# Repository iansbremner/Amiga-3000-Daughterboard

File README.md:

# Amiga-3000-Daughterboard
This is a recreation of the Rev 9 Daughterboard for the Amiga 3000
This is a 4 Layer board with signal on the upper and lower layers and a Power and Ground Plane.

When fabbing the board you will probably be asked if you want to remove the solder mask on the area for the Edge Connectors. It is fine to say Yes to this.

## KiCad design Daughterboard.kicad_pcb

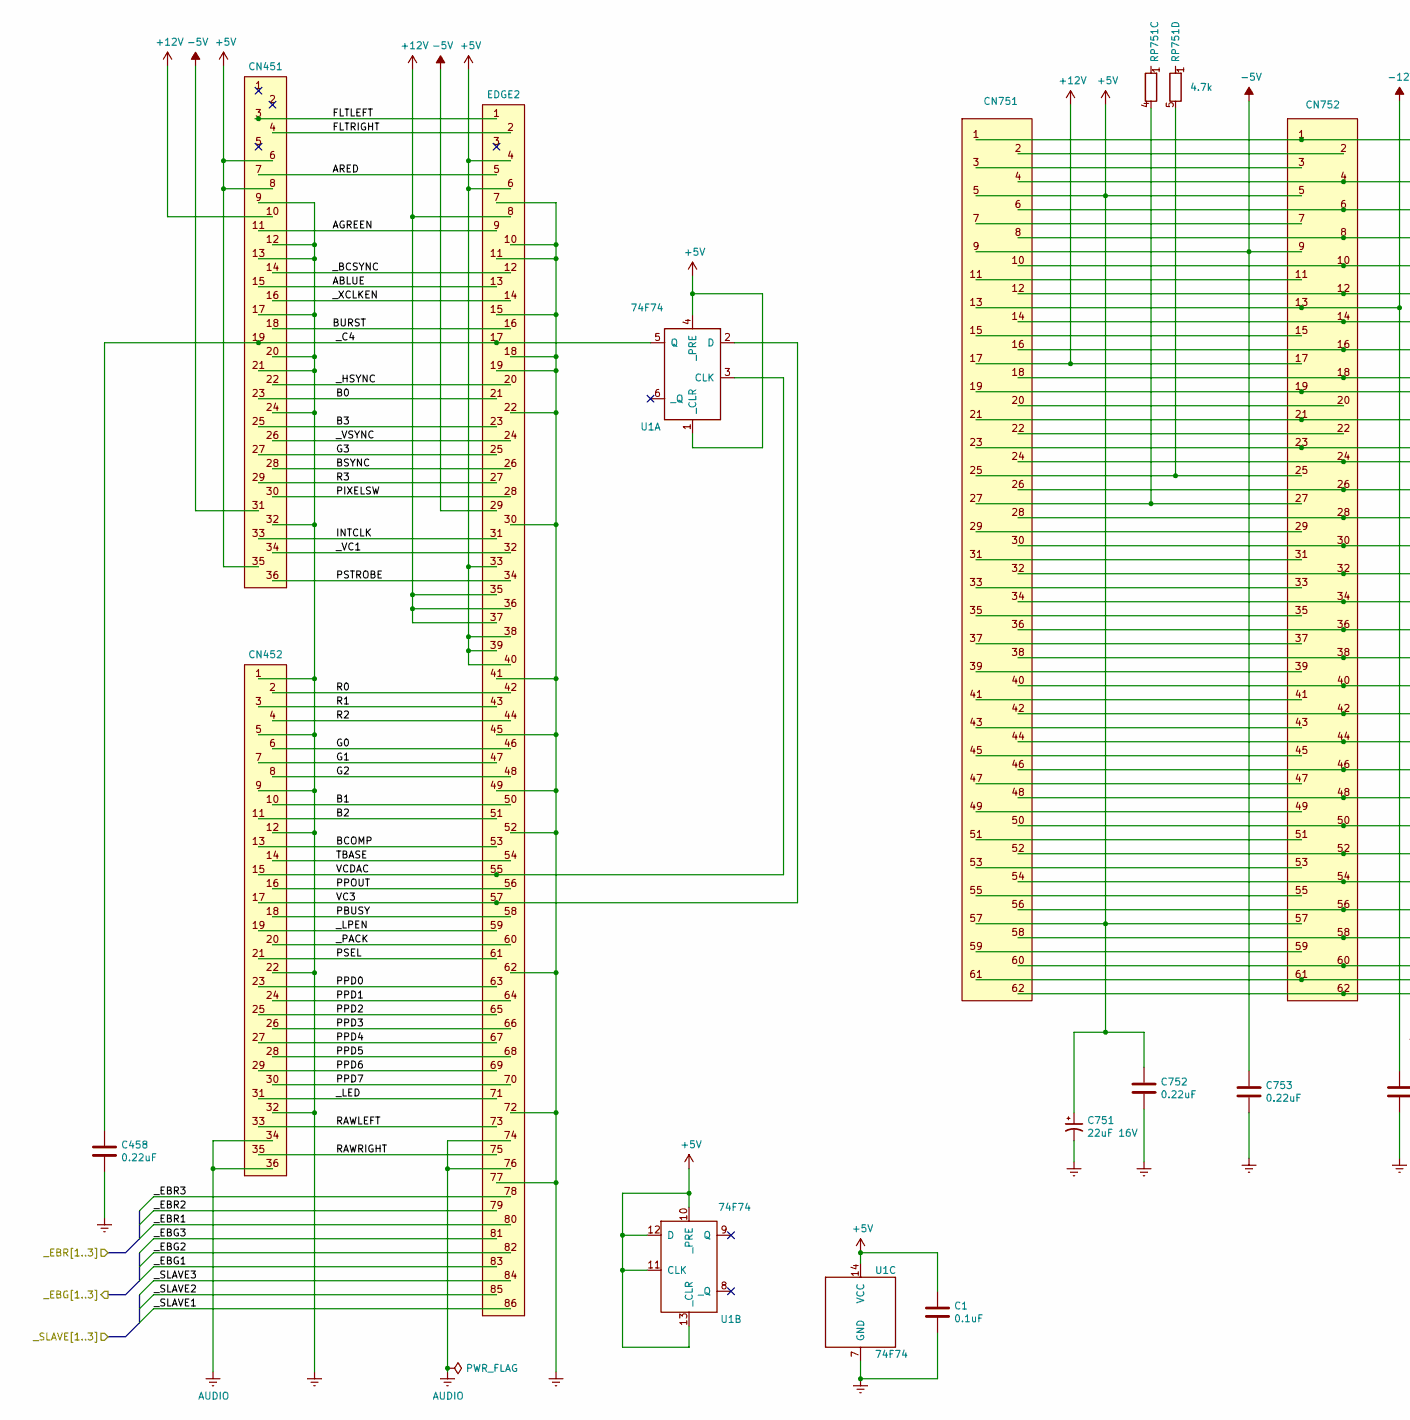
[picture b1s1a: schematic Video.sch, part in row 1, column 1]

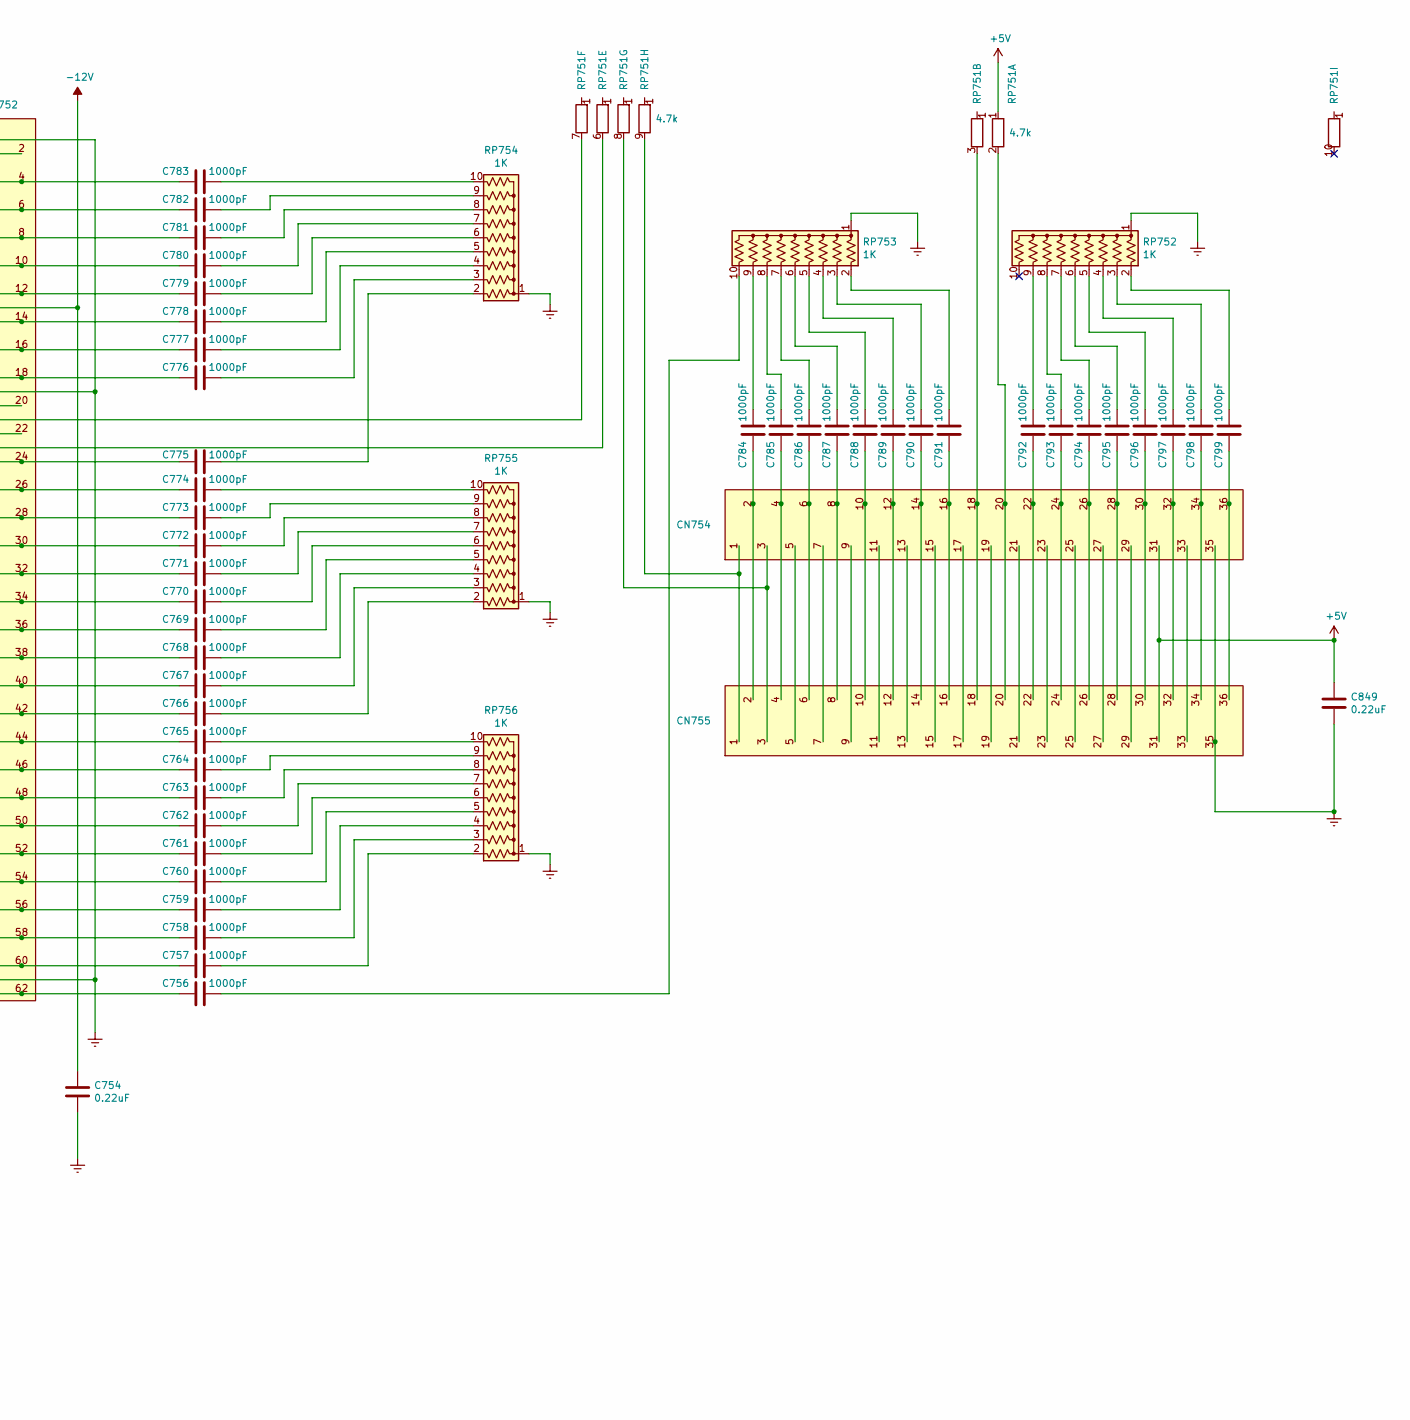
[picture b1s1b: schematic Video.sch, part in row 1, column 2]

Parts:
C1: 0.1uF; C_Axial_L5.1mm_D3.1mm_P7.50mm_Horizontal
C458, C752, C753, C754, C849: 0.22uF; C_Disc_D7.0mm_W2.5mm_P5.00mm
C751: 22uF 16V; CP_Radial_D8.0mm_P5.00mm
C756, C757, C758, C759, C760, C761, C762, C763, C764, C765, C766, C767, C768, C769, C770, C771, C772, C773, C774, C775, C776, C777, C778, C779, C780, C781, C782, C783, C784, C785, C786, C787, C788, C789, C790, C791, C792, C793, C794, C795, C796, C797, C798, C799: 1000pF; C_Rect_L4.6mm_W2.0mm_P2.50mm_MKS02_FKP02
CN451, CN452: Video_Slot; Video Slot
CN751, CN752: ISA_8_Bit; ISA 8 Bit
CN754, CN755: ISA_16_Bit_Extended; ISA 16 Bit
EDGE2: Edge2; Edge1
RP751: 4.7k; R_Array_SIP10
RP752, RP753, RP754, RP755, RP756: 1K; R_Array_SIP10
U1: 74F74; DIP-14_W7.62mm

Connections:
+5V: C1.1, C751.1, C752.1, C849.1, CN451.6, CN451.8, CN451.35, CN751.5, CN751.57, CN752.5, CN752.57, CN754.31, CN755.31, EDGE2.4, EDGE2.6, EDGE2.33, EDGE2.38, EDGE2.39, EDGE2.40, RP751.1 (R1.1), U1.1 (_CLR), U1.4 (_PRE), U1.10 (_PRE), U1.11 (CLK), U1.12 (D), U1.13 (_CLR), U1.14 (VCC); also elsewhere on the board
+12V: CN451.10, CN751.17, CN752.17, EDGE2.8, EDGE2.35, EDGE2.36, EDGE2.37; also elsewhere on the board
-5V: C753.1, CN451.31, CN751.9, CN752.9, EDGE2.29; also elsewhere on the board
-12V: C754.1, CN751.13, CN752.13; also elsewhere on the board
/Video & ISA/ABLUE: CN451.15, EDGE2.13
/Video & ISA/AGREEN: CN451.11, EDGE2.9
/Video & ISA/ARED: CN451.7, EDGE2.5
/Video & ISA/B0: CN451.23, EDGE2.21
/Video & ISA/B1: CN452.10, EDGE2.50
/Video & ISA/B2: CN452.11, EDGE2.51
/Video & ISA/B3: CN451.25, EDGE2.23
/Video & ISA/BCOMP: CN452.13, EDGE2.53
/Video & ISA/BSYNC: CN451.28, EDGE2.26
/Video & ISA/BURST: CN451.18, EDGE2.16
/Video & ISA/FLTLEFT: CN451.3, EDGE2.1
/Video & ISA/FLTRIGHT: CN451.4, EDGE2.2
/Video & ISA/G0: CN452.6, EDGE2.46
/Video & ISA/G1: CN452.7, EDGE2.47
/Video & ISA/G2: CN452.8, EDGE2.48
/Video & ISA/G3: CN451.27, EDGE2.25
/Video & ISA/INTCLK: CN451.33, EDGE2.31
/Video & ISA/PBUSY: CN452.18, EDGE2.58
/Video & ISA/PIXELSW: CN451.30, EDGE2.28
/Video & ISA/PPD0: CN452.23, EDGE2.63
/Video & ISA/PPD1: CN452.24, EDGE2.64
/Video & ISA/PPD2: CN452.25, EDGE2.65
/Video & ISA/PPD3: CN452.26, EDGE2.66
/Video & ISA/PPD4: CN452.27, EDGE2.67
/Video & ISA/PPD5: CN452.28, EDGE2.68
/Video & ISA/PPD6: CN452.29, EDGE2.69
/Video & ISA/PPD7: CN452.30, EDGE2.70
/Video & ISA/PPOUT: CN452.16, EDGE2.56
/Video & ISA/PSEL: CN452.21, EDGE2.61
/Video & ISA/PSTROBE: CN451.36, EDGE2.34
/Video & ISA/R0: CN452.2, EDGE2.42
/Video & ISA/R1: CN452.3, EDGE2.43
/Video & ISA/R2: CN452.4, EDGE2.44
/Video & ISA/R3: CN451.29, EDGE2.27
/Video & ISA/RAWLEFT: CN452.33, EDGE2.73
/Video & ISA/RAWRIGHT: CN452.35, EDGE2.75
/Video & ISA/TBASE: CN452.14, EDGE2.54
/Video & ISA/VC3: CN452.17, EDGE2.57, U1.2 (D)
/Video & ISA/VCDAC: CN452.15, EDGE2.55, U1.3 (CLK)
/Video & ISA/_BCSYNC: CN451.14, EDGE2.12
/Video & ISA/_C4: C458.1, CN451.19, EDGE2.17, U1.5 (Q)
/Video & ISA/_EBG1: EDGE2.83; also elsewhere on the board
/Video & ISA/_EBG2: EDGE2.82; also elsewhere on the board
/Video & ISA/_EBG3: EDGE2.81; also elsewhere on the board
/Video & ISA/_EBR1: EDGE2.80; also elsewhere on the board
/Video & ISA/_EBR2: EDGE2.79; also elsewhere on the board
/Video & ISA/_EBR3: EDGE2.78; also elsewhere on the board
/Video & ISA/_HSYNC: CN451.22, EDGE2.20
/Video & ISA/_LED: CN452.31, EDGE2.71
/Video & ISA/_LPEN: CN452.19, EDGE2.59
/Video & ISA/_PACK: CN452.20, EDGE2.60
/Video & ISA/_SLAVE1: EDGE2.86; also elsewhere on the board
/Video & ISA/_SLAVE2: EDGE2.85; also elsewhere on the board
/Video & ISA/_SLAVE3: EDGE2.84; also elsewhere on the board
/Video & ISA/_VC1: CN451.34, EDGE2.32
/Video & ISA/_VSYNC: CN451.26, EDGE2.24
/Video & ISA/_XCLKEN: CN451.16, EDGE2.14
AUDIO: CN452.34, CN452.36, EDGE2.74, EDGE2.76
Earth: C1.2, C458.2, C751.2, C752.2, C753.2, C754.2, C849.2, CN451.9, CN451.12, CN451.13, CN451.17, CN451.20, CN451.21, CN451.24, CN451.32, CN452.1, CN452.5, CN452.9, CN452.12, CN452.22, CN452.32, CN751.1, CN751.19, CN751.61, CN752.1, CN752.19, CN752.61, CN754.35, CN755.35, EDGE2.7, EDGE2.10, EDGE2.11, EDGE2.15, EDGE2.18, EDGE2.19, EDGE2.22, EDGE2.30, EDGE2.41, EDGE2.45, EDGE2.49, EDGE2.52, EDGE2.62, EDGE2.72, EDGE2.77, RP752.1 (common), RP753.1 (common), RP754.1 (common), RP755.1 (common), RP756.1 (common), U1.7 (GND); also elsewhere on the board
unnamed: C756.1, RP753.10 (R9)
unnamed: C756.2, CN751.62, CN752.62
unnamed: C757.1, RP756.2 (R1)
unnamed: C757.2, CN751.60, CN752.60
unnamed: C758.1, RP756.3 (R2)
unnamed: C758.2, CN751.58, CN752.58
unnamed: C759.1, RP756.4 (R3)
unnamed: C759.2, CN751.56, CN752.56
unnamed: C760.1, RP756.5 (R4)
unnamed: C760.2, CN751.54, CN752.54
unnamed: C761.1, RP756.6 (R5)
unnamed: C761.2, CN751.52, CN752.52
unnamed: C762.1, RP756.7 (R6)
unnamed: C762.2, CN751.50, CN752.50
unnamed: C763.1, RP756.8 (R7)
unnamed: C763.2, CN751.48, CN752.48
unnamed: C764.1, RP756.9 (R8)
unnamed: C764.2, CN751.46, CN752.46
unnamed: C765.1, RP756.10 (R9)
unnamed: C765.2, CN751.44, CN752.44
unnamed: C766.1, RP755.2 (R1)
unnamed: C766.2, CN751.42, CN752.42
unnamed: C767.1, RP755.3 (R2)
unnamed: C767.2, CN751.40, CN752.40
unnamed: C768.1, RP755.4 (R3)
unnamed: C768.2, CN751.38, CN752.38
unnamed: C769.1, RP755.5 (R4)
unnamed: C769.2, CN751.36, CN752.36
unnamed: C770.1, RP755.6 (R5)
unnamed: C770.2, CN751.34, CN752.34
unnamed: C771.1, RP755.7 (R6)
unnamed: C771.2, CN751.32, CN752.32
unnamed: C772.1, RP755.8 (R7)
unnamed: C772.2, CN751.30, CN752.30
unnamed: C773.1, RP755.9 (R8)
unnamed: C773.2, CN751.28, CN752.28
unnamed: C774.1, RP755.10 (R9)
unnamed: C774.2, CN751.26, CN752.26
unnamed: C775.1, RP754.2 (R1)
unnamed: C775.2, CN751.24, CN752.24
unnamed: C776.1, RP754.3 (R2)
unnamed: C776.2, CN751.18, CN752.18
unnamed: C777.1, RP754.4 (R3)
unnamed: C777.2, CN751.16, CN752.16
unnamed: C778.1, RP754.5 (R4)
unnamed: C778.2, CN751.14, CN752.14
unnamed: C779.1, RP754.6 (R5)
unnamed: C779.2, CN751.12, CN752.12
unnamed: C780.1, RP754.7 (R6)
unnamed: C780.2, CN751.10, CN752.10
unnamed: C781.1, RP754.8 (R7)
unnamed: C781.2, CN751.8, CN752.8
unnamed: C782.1, RP754.9 (R8)
unnamed: C782.2, CN751.6, CN752.6
unnamed: C783.1, RP754.10 (R9)
unnamed: C783.2, CN751.4, CN752.4
unnamed: C784.1, RP753.9 (R8)
unnamed: C784.2, CN754.2, CN755.2
unnamed: C785.1, RP753.8 (R7)
unnamed: C785.2, CN754.4, CN755.4
unnamed: C786.1, RP753.7 (R6)
unnamed: C786.2, CN754.6, CN755.6
unnamed: C787.1, RP753.6 (R5)
unnamed: C787.2, CN754.8, CN755.8
unnamed: C788.1, RP753.5 (R4)
unnamed: C788.2, CN754.10, CN755.10
unnamed: C789.1, RP753.4 (R3)
unnamed: C789.2, CN754.12, CN755.12
unnamed: C790.1, RP753.3 (R2)
unnamed: C790.2, CN754.14, CN755.14
unnamed: C791.1, RP753.2 (R1)
unnamed: C791.2, CN754.16, CN755.16
unnamed: C792.1, RP752.9 (R8)
unnamed: C792.2, CN754.22, CN755.22
unnamed: C793.1, RP752.8 (R7)
unnamed: C793.2, CN754.24, CN755.24
unnamed: C794.1, RP752.7 (R6)
unnamed: C794.2, CN754.26, CN755.26
unnamed: C795.1, RP752.6 (R5)
unnamed: C795.2, CN754.28, CN755.28
unnamed: C796.1, RP752.5 (R4)
unnamed: C796.2, CN754.30, CN755.30
unnamed: C797.1, RP752.4 (R3)
unnamed: C797.2, CN754.32, CN755.32
unnamed: C798.1, RP752.3 (R2)
unnamed: C798.2, CN754.34, CN755.34
unnamed: C799.1, RP752.2 (R1)
unnamed: C799.2, CN754.36, CN755.36
unnamed: CN751.2, CN752.2
unnamed: CN751.3, CN752.3
unnamed: CN751.7, CN752.7
unnamed: CN751.11, CN752.11
unnamed: CN751.15, CN752.15
unnamed: CN751.20, CN752.20
unnamed: CN751.21, CN752.21, RP751.7 (R6.2)
unnamed: CN751.22, CN752.22
unnamed: CN751.23, CN752.23, RP751.6 (R5.2)
unnamed: CN751.25, CN752.25, RP751.5 (R4.2)
unnamed: CN751.27, CN752.27, RP751.4 (R3.2)
unnamed: CN751.29, CN752.29
unnamed: CN751.31, CN752.31
unnamed: CN751.33, CN752.33
unnamed: CN751.35, CN752.35
unnamed: CN751.37, CN752.37
unnamed: CN751.39, CN752.39
unnamed: CN751.41, CN752.41
unnamed: CN751.43, CN752.43
unnamed: CN751.45, CN752.45
unnamed: CN751.47, CN752.47
unnamed: CN751.49, CN752.49
unnamed: CN751.51, CN752.51
unnamed: CN751.53, CN752.53
unnamed: CN751.55, CN752.55
unnamed: CN751.59, CN752.59
unnamed: CN754.1, CN755.1, RP751.9 (R8.2)
unnamed: CN754.3, CN755.3, RP751.8 (R7.2)
unnamed: CN754.5, CN755.5
unnamed: CN754.7, CN755.7
unnamed: CN754.9, CN755.9
unnamed: CN754.11, CN755.11
unnamed: CN754.13, CN755.13
unnamed: CN754.15, CN755.15
unnamed: CN754.17, CN755.17
unnamed: CN754.18, CN755.18, RP751.3 (R2.2)
unnamed: CN754.19, CN755.19
unnamed: CN754.20, CN755.20, RP751.2 (R1.2)
unnamed: CN754.21, CN755.21
unnamed: CN754.23, CN755.23
unnamed: CN754.25, CN755.25
unnamed: CN754.27, CN755.27
unnamed: CN754.29, CN755.29
unnamed: CN754.33, CN755.33

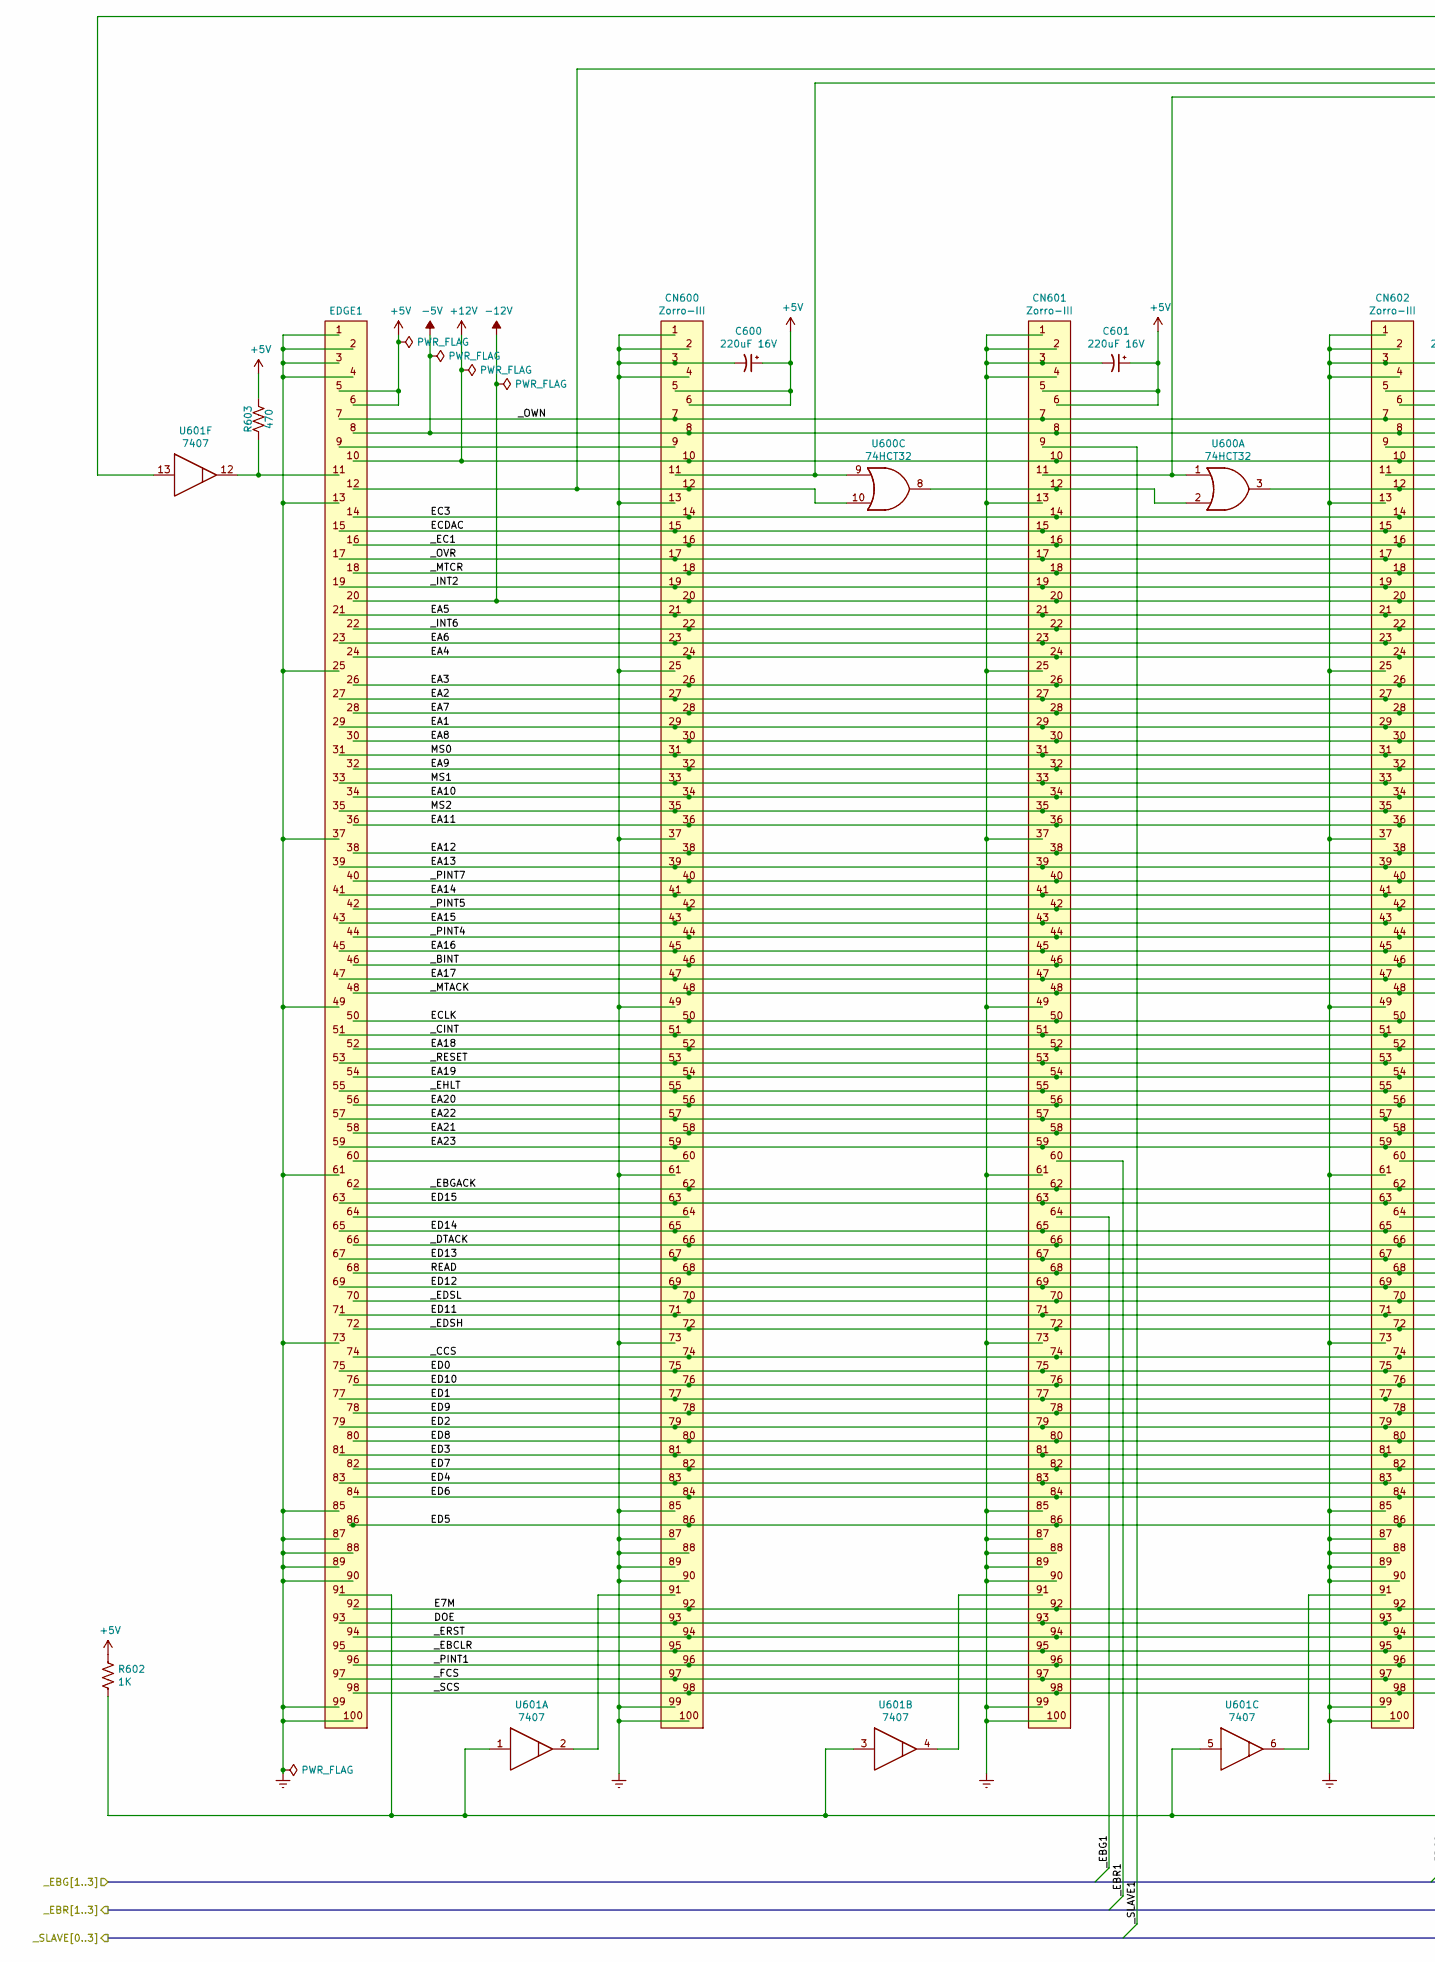
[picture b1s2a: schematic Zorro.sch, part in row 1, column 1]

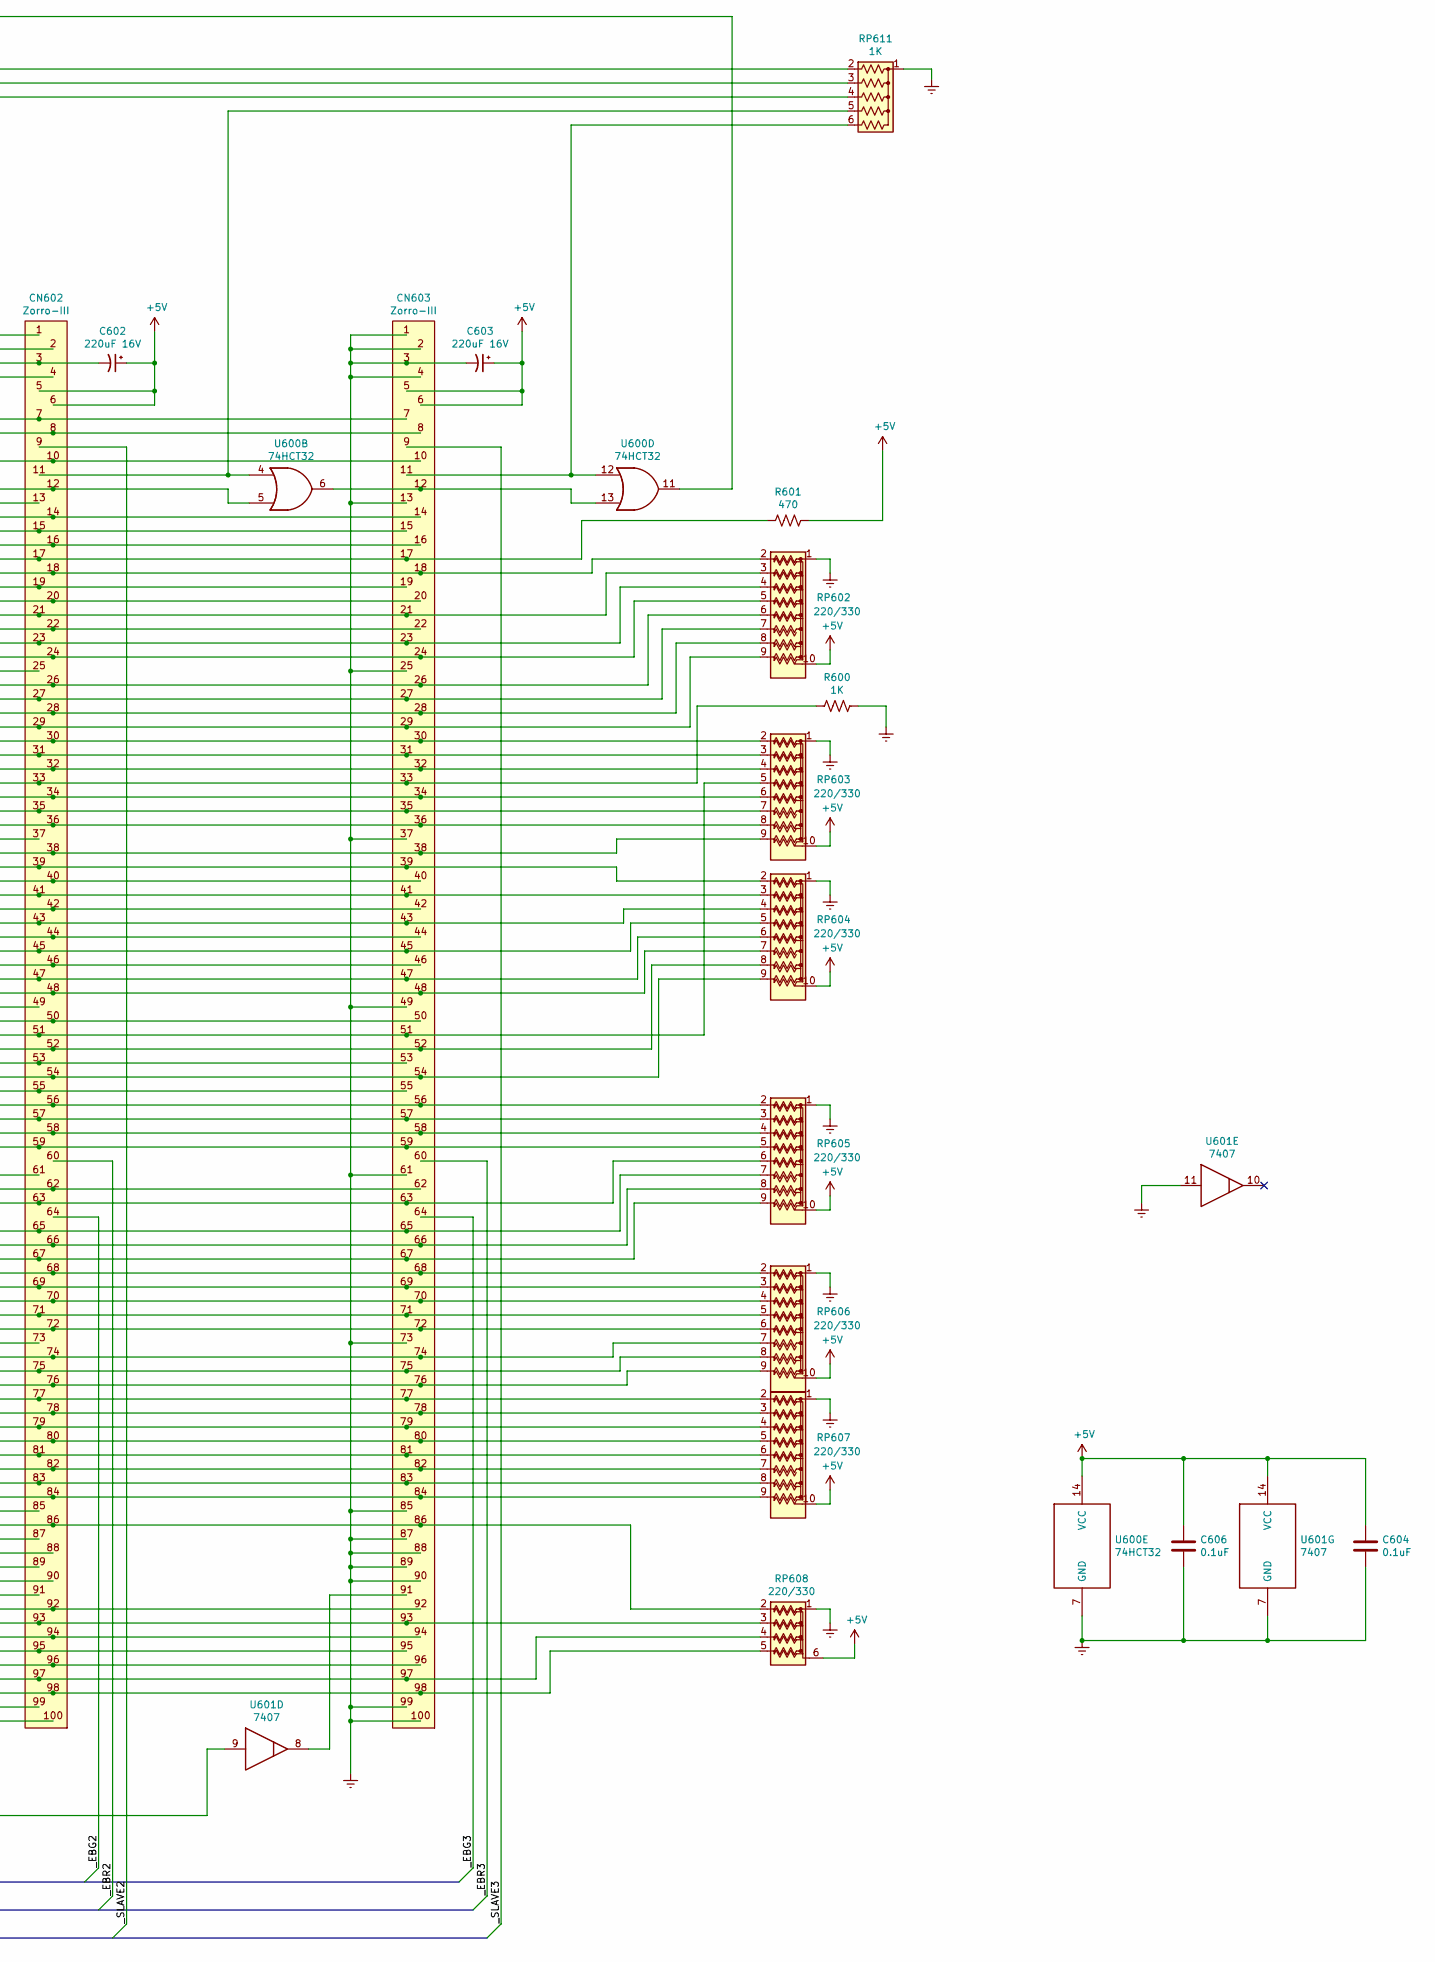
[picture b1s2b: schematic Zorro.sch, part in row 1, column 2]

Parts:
C600, C601, C602, C603: 220uF 16V; CP_Axial_L21.0mm_D8.0mm_P28.00mm_Horizontal
C604, C606: 0.1uF; C_Axial_L5.1mm_D3.1mm_P7.50mm_Horizontal
CN600, CN601, CN602, CN603: Zorro-III
EDGE1: Edge1; Edge2
R600, R602: 1K; Resistor
R601, R603: 470; Resistor
RP602, RP603, RP604, RP605, RP606, RP607: 220/330; R_Array_SIP10
RP608: 220/330; R_Array_SIP6
RP611: 1K; R_Array_SIP6
U600: 74HCT32; DIP-14_W7.62mm_Socket
U601: 7407; DIP-14_W7.62mm

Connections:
+5V: C600.1, C601.1, C602.1, C603.1, C604.1, C606.1, CN600.5, CN600.6, CN601.5, CN601.6, CN602.5, CN602.6, CN603.5, CN603.6, EDGE1.5, EDGE1.6, R601.1, R602.1, R603.1, RP602.10 (R7), RP603.10 (R7), RP604.10 (R7), RP605.10 (R7), RP606.10 (R7), RP607.10 (R7), RP608.6 (R7), U600.14 (VCC), U601.14 (VCC); also elsewhere on the board
+12V: CN600.10, CN601.10, CN602.10, CN603.10, EDGE1.10; also elsewhere on the board
-5V: CN600.8, CN601.8, CN602.8, CN603.8, EDGE1.8; also elsewhere on the board
-12V: CN600.20, CN601.20, CN602.20, CN603.20, EDGE1.20; also elsewhere on the board
/Video & ISA/_EBG1: CN601.64; also elsewhere on the board
/Video & ISA/_EBG2: CN602.64; also elsewhere on the board
/Video & ISA/_EBG3: CN603.64; also elsewhere on the board
/Video & ISA/_EBR1: CN601.60; also elsewhere on the board
/Video & ISA/_EBR2: CN602.60; also elsewhere on the board
/Video & ISA/_EBR3: CN603.60; also elsewhere on the board
/Video & ISA/_SLAVE1: CN601.9; also elsewhere on the board
/Video & ISA/_SLAVE2: CN602.9; also elsewhere on the board
/Video & ISA/_SLAVE3: CN603.9; also elsewhere on the board
/Zorro/DOE: CN600.93, CN601.93, CN602.93, CN603.93, EDGE1.93, RP608.3 (R2)
/Zorro/E7M: CN600.92, CN601.92, CN602.92, CN603.92, EDGE1.92
/Zorro/EA1: CN600.29, CN601.29, CN602.29, CN603.29, EDGE1.29, RP602.9 (R6)
/Zorro/EA2: CN600.27, CN601.27, CN602.27, CN603.27, EDGE1.27, RP602.7 (R6)
/Zorro/EA3: CN600.26, CN601.26, CN602.26, CN603.26, EDGE1.26, RP602.6 (R5)
/Zorro/EA4: CN600.24, CN601.24, CN602.24, CN603.24, EDGE1.24, RP602.5 (R4)
/Zorro/EA5: CN600.21, CN601.21, CN602.21, CN603.21, EDGE1.21, RP602.3 (R2)
/Zorro/EA6: CN600.23, CN601.23, CN602.23, CN603.23, EDGE1.23, RP602.4 (R3)
/Zorro/EA7: CN600.28, CN601.28, CN602.28, CN603.28, EDGE1.28, RP602.8 (R6)
/Zorro/EA8: CN600.30, CN601.30, CN602.30, CN603.30, EDGE1.30, RP603.2 (R1)
/Zorro/EA9: CN600.32, CN601.32, CN602.32, CN603.32, EDGE1.32, RP603.4 (R3)
/Zorro/EA10: CN600.34, CN601.34, CN602.34, CN603.34, EDGE1.34, RP603.6 (R5)
/Zorro/EA11: CN600.36, CN601.36, CN602.36, CN603.36, EDGE1.36, RP603.8 (R6)
/Zorro/EA12: CN600.38, CN601.38, CN602.38, CN603.38, EDGE1.38, RP603.9 (R6)
/Zorro/EA13: CN600.39, CN601.39, CN602.39, CN603.39, EDGE1.39, RP604.2 (R1)
/Zorro/EA14: CN600.41, CN601.41, CN602.41, CN603.41, EDGE1.41, RP604.3 (R2)
/Zorro/EA15: CN600.43, CN601.43, CN602.43, CN603.43, EDGE1.43, RP604.4 (R3)
/Zorro/EA16: CN600.45, CN601.45, CN602.45, CN603.45, EDGE1.45, RP604.5 (R4)
/Zorro/EA17: CN600.47, CN601.47, CN602.47, CN603.47, EDGE1.47, RP604.6 (R5)
/Zorro/EA18: CN600.52, CN601.52, CN602.52, CN603.52, EDGE1.52, RP604.8 (R6)
/Zorro/EA19: CN600.54, CN601.54, CN602.54, CN603.54, EDGE1.54, RP604.9 (R6)
/Zorro/EA20: CN600.56, CN601.56, CN602.56, CN603.56, EDGE1.56, RP605.2 (R1)
/Zorro/EA21: CN600.58, CN601.58, CN602.58, CN603.58, EDGE1.58, RP605.4 (R3)
/Zorro/EA22: CN600.57, CN601.57, CN602.57, CN603.57, EDGE1.57, RP605.3 (R2)
/Zorro/EA23: CN600.59, CN601.59, CN602.59, CN603.59, EDGE1.59, RP605.5 (R4)
/Zorro/EC3: CN600.14, CN601.14, CN602.14, CN603.14, EDGE1.14
/Zorro/ECDAC: CN600.15, CN601.15, CN602.15, CN603.15, EDGE1.15
/Zorro/ECLK: CN600.50, CN601.50, CN602.50, CN603.50, EDGE1.50
/Zorro/ED0: CN600.75, CN601.75, CN602.75, CN603.75, EDGE1.75, RP606.8 (R6)
/Zorro/ED1: CN600.77, CN601.77, CN602.77, CN603.77, EDGE1.77, RP607.2 (R1)
/Zorro/ED2: CN600.79, CN601.79, CN602.79, CN603.79, EDGE1.79, RP607.4 (R3)
/Zorro/ED3: CN600.81, CN601.81, CN602.81, CN603.81, EDGE1.81, RP607.6 (R5)
/Zorro/ED4: CN600.83, CN601.83, CN602.83, CN603.83, EDGE1.83, RP607.8 (R6)
/Zorro/ED5: CN600.86, CN601.86, CN602.86, CN603.86, EDGE1.86, RP608.2 (R1)
/Zorro/ED6: CN600.84, CN601.84, CN602.84, CN603.84, EDGE1.84, RP607.9 (R6)
/Zorro/ED7: CN600.82, CN601.82, CN602.82, CN603.82, EDGE1.82, RP607.7 (R6)
/Zorro/ED8: CN600.80, CN601.80, CN602.80, CN603.80, EDGE1.80, RP607.5 (R4)
/Zorro/ED9: CN600.78, CN601.78, CN602.78, CN603.78, EDGE1.78, RP607.3 (R2)
/Zorro/ED10: CN600.76, CN601.76, CN602.76, CN603.76, EDGE1.76, RP606.9 (R6)
/Zorro/ED11: CN600.71, CN601.71, CN602.71, CN603.71, EDGE1.71, RP606.5 (R4)
/Zorro/ED12: CN600.69, CN601.69, CN602.69, CN603.69, EDGE1.69, RP606.3 (R2)
/Zorro/ED13: CN600.67, CN601.67, CN602.67, CN603.67, EDGE1.67, RP605.9 (R6)
/Zorro/ED14: CN600.65, CN601.65, CN602.65, CN603.65, EDGE1.65, RP605.7 (R6)
/Zorro/ED15: CN600.63, CN601.63, CN602.63, CN603.63, EDGE1.63, RP605.6 (R5)
/Zorro/MS0: CN600.31, CN601.31, CN602.31, CN603.31, EDGE1.31, RP603.3 (R2)
/Zorro/MS1: CN600.33, CN601.33, CN602.33, CN603.33, EDGE1.33, R600.2
/Zorro/MS2: CN600.35, CN601.35, CN602.35, CN603.35, EDGE1.35, RP603.7 (R6)
/Zorro/READ: CN600.68, CN601.68, CN602.68, CN603.68, EDGE1.68, RP606.2 (R1)
/Zorro/_BINT: CN600.46, CN601.46, CN602.46, CN603.46, EDGE1.46
/Zorro/_CCS: CN600.74, CN601.74, CN602.74, CN603.74, EDGE1.74, RP606.7 (R6)
/Zorro/_CINT: CN600.51, CN601.51, CN602.51, CN603.51, EDGE1.51, RP603.5 (R4)
/Zorro/_DTACK: CN600.66, CN601.66, CN602.66, CN603.66, EDGE1.66, RP605.8 (R6)
/Zorro/_EBCLR: CN600.95, CN601.95, CN602.95, CN603.95, EDGE1.95
/Zorro/_EBGACK: CN600.62, CN601.62, CN602.62, CN603.62, EDGE1.62
/Zorro/_EC1: CN600.16, CN601.16, CN602.16, CN603.16, EDGE1.16
/Zorro/_EDSH: CN600.72, CN601.72, CN602.72, CN603.72, EDGE1.72, RP606.6 (R5)
/Zorro/_EDSL: CN600.70, CN601.70, CN602.70, CN603.70, EDGE1.70, RP606.4 (R3)
/Zorro/_EHLT: CN600.55, CN601.55, CN602.55, CN603.55, EDGE1.55
/Zorro/_ERST: CN600.94, CN601.94, CN602.94, CN603.94, EDGE1.94
/Zorro/_FCS: CN600.97, CN601.97, CN602.97, CN603.97, EDGE1.97, RP608.4 (R3)
/Zorro/_INT2: CN600.19, CN601.19, CN602.19, CN603.19, EDGE1.19
/Zorro/_INT6: CN600.22, CN601.22, CN602.22, CN603.22, EDGE1.22
/Zorro/_MTACK: CN600.48, CN601.48, CN602.48, CN603.48, EDGE1.48, RP604.7 (R6)
/Zorro/_MTCR: CN600.18, CN601.18, CN602.18, CN603.18, EDGE1.18, RP602.2 (R1)
/Zorro/_OVR: CN600.17, CN601.17, CN602.17, CN603.17, EDGE1.17, R601.2
/Zorro/_OWN: CN600.7, CN601.7, CN602.7, CN603.7, EDGE1.7
/Zorro/_PINT1: CN600.96, CN601.96, CN602.96, CN603.96, EDGE1.96
/Zorro/_PINT4: CN600.44, CN601.44, CN602.44, CN603.44, EDGE1.44
/Zorro/_PINT5: CN600.42, CN601.42, CN602.42, CN603.42, EDGE1.42
/Zorro/_PINT7: CN600.40, CN601.40, CN602.40, CN603.40, EDGE1.40
/Zorro/_RESET: CN600.53, CN601.53, CN602.53, CN603.53, EDGE1.53
/Zorro/_SCS: CN600.98, CN601.98, CN602.98, CN603.98, EDGE1.98, RP608.5 (R4)
Earth: C600.2, C601.2, C602.2, C603.2, C604.2, C606.2, CN600.1, CN600.2, CN600.3, CN600.4, CN600.13, CN600.25, CN600.37, CN600.49, CN600.61, CN600.73, CN600.85, CN600.87, CN600.88, CN600.89, CN600.90, CN600.99, CN600.100, CN601.1, CN601.2, CN601.3, CN601.4, CN601.13, CN601.25, CN601.37, CN601.49, CN601.61, CN601.73, CN601.85, CN601.87, CN601.88, CN601.89, CN601.90, CN601.99, CN601.100, CN602.1, CN602.2, CN602.3, CN602.4, CN602.13, CN602.25, CN602.37, CN602.49, CN602.61, CN602.73, CN602.85, CN602.87, CN602.88, CN602.89, CN602.90, CN602.99, CN602.100, CN603.1, CN603.2, CN603.3, CN603.4, CN603.13, CN603.25, CN603.37, CN603.49, CN603.61, CN603.73, CN603.85, CN603.87, CN603.88, CN603.89, CN603.90, CN603.99, CN603.100, EDGE1.1, EDGE1.2, EDGE1.3, EDGE1.4, EDGE1.13, EDGE1.25, EDGE1.37, EDGE1.49, EDGE1.61, EDGE1.73, EDGE1.85, EDGE1.87, EDGE1.88, EDGE1.89, EDGE1.90, EDGE1.99, EDGE1.100, R600.1, RP602.1 (common), RP603.1 (common), RP604.1 (common), RP605.1 (common), RP606.1 (common), RP607.1 (common), RP608.1 (common), RP611.1 (common), U600.7 (GND), U601.7 (GND), U601.11; also elsewhere on the board
unnamed: CN600.9, EDGE1.9
unnamed: CN600.11, RP611.3 (R2), U600.9
unnamed: CN600.12, EDGE1.12, RP611.2 (R1), U600.10
unnamed: CN600.60, EDGE1.60
unnamed: CN600.64, EDGE1.64
unnamed: CN600.91, U601.2
unnamed: CN601.11, RP611.4 (R3), U600.1
unnamed: CN601.12, U600.2, U600.8
unnamed: CN601.91, U601.4
unnamed: CN602.11, RP611.5 (R4), U600.4
unnamed: CN602.12, U600.3, U600.5
unnamed: CN602.91, U601.6
unnamed: CN603.11, RP611.6 (R5), U600.12
unnamed: CN603.12, U600.6, U600.13
unnamed: CN603.91, U601.8
unnamed: EDGE1.11, R603.2, U601.12
unnamed: EDGE1.91, R602.2, U601.1, U601.3, U601.5, U601.9
unnamed: U600.11, U601.13

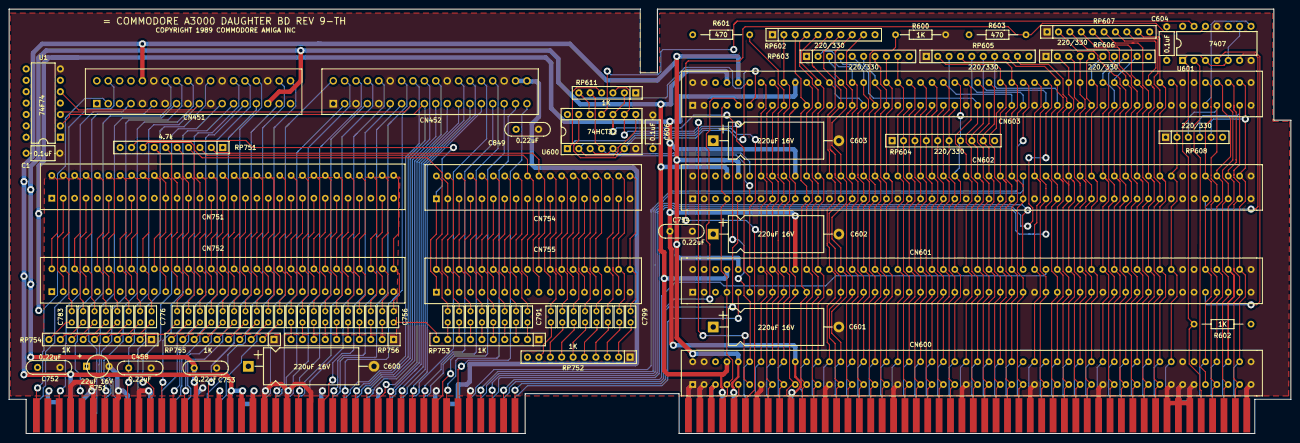
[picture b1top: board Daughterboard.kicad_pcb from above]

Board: 4 copper layers, 285.8 x 94.6 mm, 90 parts (0 on the bottom side), 285 nets.

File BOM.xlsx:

Id | Designator | Package | Quantity | Designation | Part Number | URL | Unit Price | Total Cost
1 | CN752,CN751 | Standard Card Edge Connectors 100 VRT 062DP | 2 | ISA 8 Bit Connector | 6-5530843-5 | https://www.mouser.co.uk/ProductDetail/TE-Connectivity/6-553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 | 3.18 | 6.36
2 | C751 | CP_Radial_D8.0mm_P5.00mm | 1 | 22uF 16V | ECA-1CEN220 | https://www.mouser.co.uk/ProductDetail/Panasonic/ECA-1CEN220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 | 0.26900000000000002 | 0.26900000000000002
3 | CN755,CN754 | Standard Card Edge Connectors 36 VRT 036DP | 2 | ISA 16 Bit Extended Connector | 2-5530843-7 | https://www.mouser.co.uk/ProductDetail/TE-Connectivity/2-553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 | 2.14 | 4.28
4 | RP752,RP753,RP754,RP755,RP756 | R_Array_SIP10 | 5 | 1K | 4610M-101-102LF | https://www.mouser.co.uk/ProductDetail/Bourns/4610M-101-102L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 | 0.46899999999999997 | 2.3449999999999998
5 | C458,C752,C753,C754,C849 | C_Disc_D7.0mm_W2.5mm_P5.00mm | 5 | 0.22uF | A224K20X7RF5UAAP | https://www.mouser.co.uk/ProductDetail/Vishay-BC-Components/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 | 0.42 | 2.1
6 | CN451,CN452 | Standard Card Edge Connectors 36 Position | 2 | Video Slot | 2-5530843-7 | https://www.mouser.co.uk/ProductDetail/TE-Connectivity/2-553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 | 2.14 | 4.28
7 | CN602,CN603,CN601,CN600 | Standard Card Edge Connectors CONN SEC II 100POS 100C/L | 4 | Zorro-III | 2-5530843-2 | https://www.mouser.co.uk/ProductDetail/TE-Connectivity-AMP/2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 | 6.41 | 25.64
8 | R601,R603 | Resistor | 2 | 470 | SFR2500004700JA500 | https://www.mouser.co.uk/ProductDetail/Vishay-BC-Components/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 | 0.1 | 0.2
9 | C602,C603,C601,C600 | CP_Axial_L21.0mm_D8.0mm_P28.00mm_Horizontal | 4 | 220uF 16V | MAL203135221E3 | https://www.mouser.co.uk/ProductDetail/Vishay-BC-Components/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 | 1.48 | 5.92
10 | R602,R600 | Resistor | 2 | 1K | MRS16000C1001FC100 | https://www.mouser.co.uk/ProductDetail/Vishay-BC-Components/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 | 0.25 | 0.5
12 | U1,U601U600 | DIP-14_W7.62mm_Socket | 3 | DIP Socket | 110-43-314-41-001000 | https://www.mouser.co.uk/ProductDetail/Mill-Max/110-43-314-4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 | 1.1100000000000001 | 3.33
13 | C784,C785,C788,C786,C787,C789,C790,C793,C794,C792,C795,C756,C757,C758,C759,C760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 | C_Rect_L4.6mm_W2.0mm_P2.50mm_MKS02_FKP02 | 44 | 1000pF | A102K15X7RF5UAAP | https://www.mouser.co.uk/ProductDetail/Vishay-BC-Components/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 | 0.26 | 11.440000000000001
15 | RP608 | R_Array_SIP6 | 1 | 220/330 | 4606X-104-221/331L | https://www.mouser.co.uk/ProductDetail/Bourns/4606X-104-221-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 | 0.56999999999999995 | 0.56999999999999995
16 | RP603,RP602,RP604,RP605,RP606,RP607 | R_Array_SIP10 | 6 | 220/330 | 4610X-104-221/331LF | https://www.mouser.co.uk/ProductDetail/Bourns/4606X-104-221-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 | 0.50700000000000001 | 3.0419999999999998
18 | C1,C604,C606 | C_Axial_L5.1mm_D3.1mm_P7.50mm_Horizontal | 3 | 0.1uF | A104K15X7RH5UAAP |  | 0.42 | 1.26
19 | RP611 | R_Array_SIP6 | 1 | 1K | 4606M-101-102LF | https://www.mouser.co.uk/ProductDetail/Bourns/4606M-101-102L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 | 0.51 | 0.51
20 | RP751 | R_Array_SIP10 | 1 | 4.7k | 4610H-101-472LF | https://www.mouser.co.uk/ProductDetail/Bourns/4610H-101-472L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 | 0.55000000000000004 | 0.55000000000000004
21 | U600 | DIP-14_W7.62mm | 1 | 74HCT32 | CD74HCT32EE4 | https://www.mouser.co.uk/ProductDetail/Texas-Instruments/CD7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 | 0.56000000000000005 | 0.56000000000000005
22 | U601 | DIP-14_W7.62mm | 1 | 7407 | SN7407N | https://www.mouser.co.uk/ProductDetail/Texas-Instruments/SN7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 | 0.91 | 0.91
23 | U1 | DIP-14_W7.62mm | 1 | 74F74 | SN74F74N | https://www.mouser.co.uk/ProductDetail/Texas-Instruments/SN7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 | 0.51 | 0.51
 |  |  |  |  |  |  |  | 74.576000000000008

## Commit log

2022-02-06 Amended Layout to resolve potential short and move upper notch

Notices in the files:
Daughterboard.kicad_pcb:
COPYRIGHT 1989 COMMODORE AMIGA INC
